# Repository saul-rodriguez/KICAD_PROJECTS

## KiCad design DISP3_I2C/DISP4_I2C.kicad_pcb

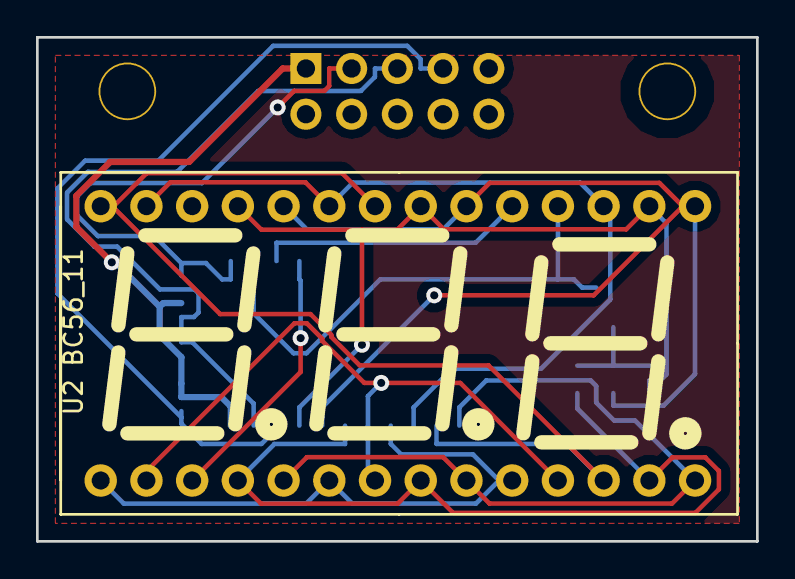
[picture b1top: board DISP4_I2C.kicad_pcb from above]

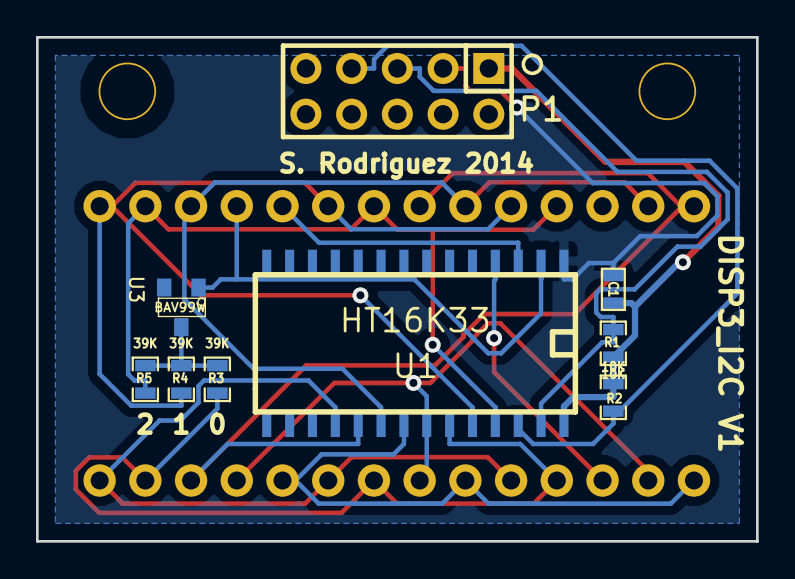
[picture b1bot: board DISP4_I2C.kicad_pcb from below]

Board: 2 copper layers, 40.0 x 28.0 mm, 12 parts (9 on the bottom side), 16 nets.

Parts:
C1: 0.1u; SM0603
P1: CONN_5X2; Pin_Header_Straight_2x05
P2, P3: CONN_1; Mhole
R1, R2: 10K; SM0603_Resistor
R3, R4, R5: 39K; SM0603_Resistor
U1: HT16K33; SO28
U2: BC56_11
U3: BAV99W; SOT23-SPECIAL

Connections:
+5V: C1.1, P1.1, R1.1, R2.1, U1.28
/A: R5.1, U1.25, U2.16, U2.21, U2.25
/B: R4.1, U1.24, U2.15, U2.20, U2.24
/C: R3.1, U1.23, U2.4, U2.8, U2.13
/COM0: U1.2, U2.18, U3.1
/COM1: U1.3, U2.19
/COM2: U1.4, U2.3
/D: U1.22, U2.2, U2.7, U2.11
/DP: U1.18, U2.5, U2.9, U2.14
/E: U1.21, U2.1, U2.6, U2.10
/F: U1.20, U2.17, U2.23, U2.27
/G: U1.19, U2.12, U2.22, U2.28
/SCL: P1.7, R2.2, U1.26
/SDA: P1.5, R1.2, U1.27
GND: C1.2, P1.3, U1.1
unnamed: R3.2, R4.2, R5.2, U3.2

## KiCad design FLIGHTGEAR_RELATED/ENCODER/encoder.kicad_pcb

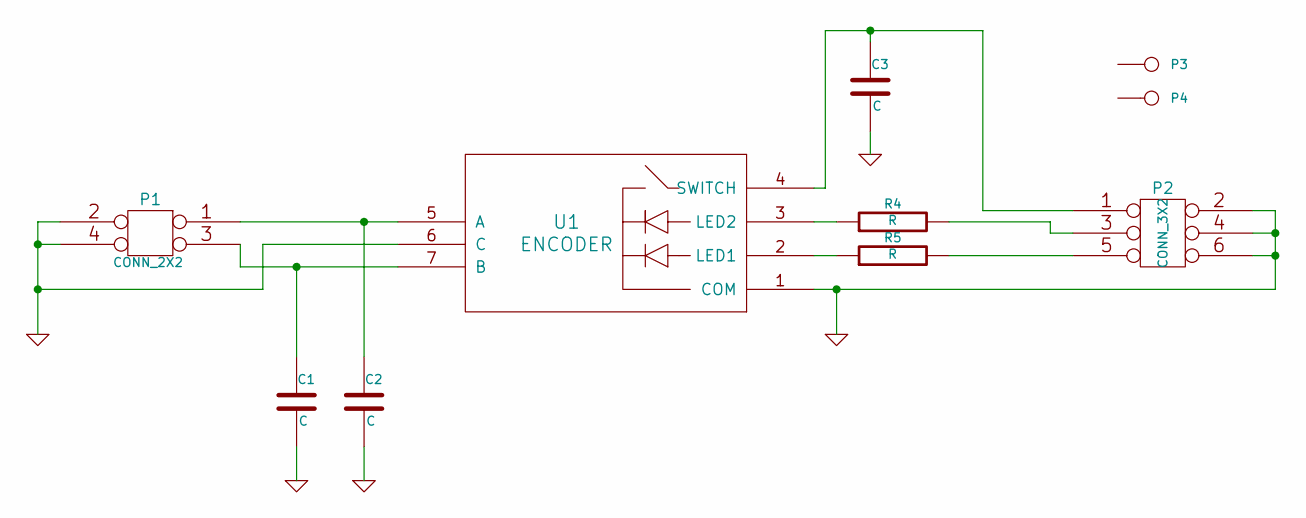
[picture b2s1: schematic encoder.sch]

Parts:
C1, C2, C3: C
P1: CONN_2X2
P2: CONN_3X2
P3, P4: CONN_1
R4, R5: R
U1: ENCODER

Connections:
GND: C1.2, C2.2, C3.2, P1.2, P1.4, P2.2, P2.4, P2.6, U1.1 (COM), U1.6 (C)
unnamed: C1.1, P1.3, U1.7 (B)
unnamed: C2.1, P1.1, U1.5 (A)
unnamed: C3.1, P2.1, U1.4 (SWITCH)
unnamed: P2.3, R4.2
unnamed: P2.5, R5.2
unnamed: R4.1, U1.3 (LED2)
unnamed: R5.1, U1.2 (LED1)

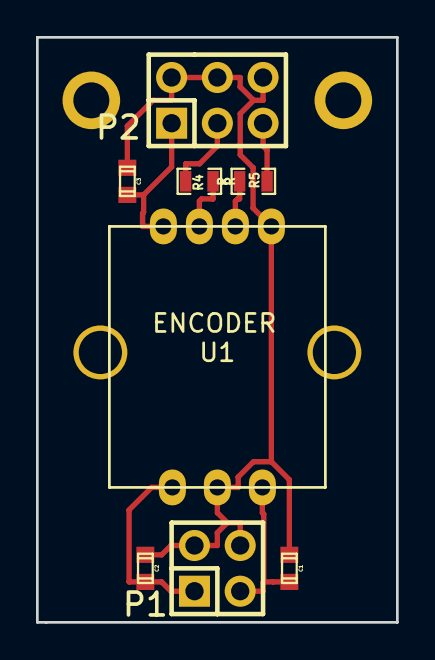
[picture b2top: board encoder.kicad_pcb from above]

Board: 2 copper layers, 20.0 x 32.5 mm, 10 parts (0 on the bottom side), 8 nets.

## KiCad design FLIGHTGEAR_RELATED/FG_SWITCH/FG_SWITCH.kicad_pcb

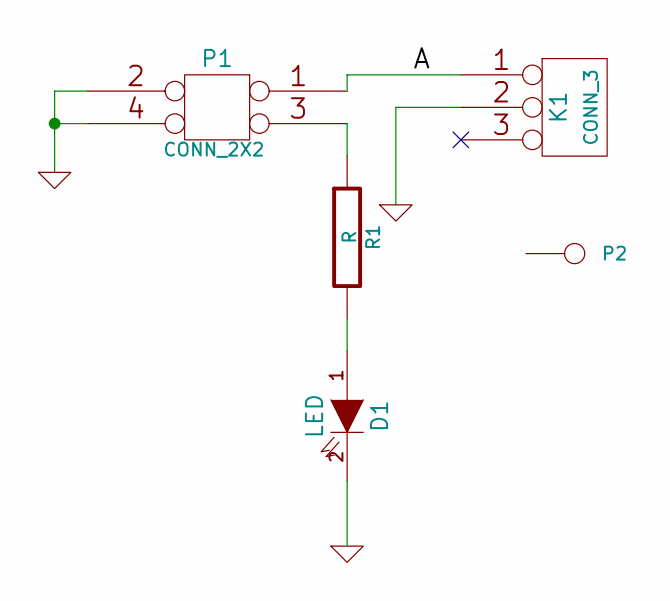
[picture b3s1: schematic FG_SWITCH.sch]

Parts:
D1: LED
K1: CONN_3
P1: CONN_2X2
P2: CONN_1
R1: R

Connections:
/A: K1.1, P1.1
GND: D1.2 (K), K1.2 (PM), P1.2, P1.4
unnamed: D1.1 (A), R1.2
unnamed: P1.3, R1.1

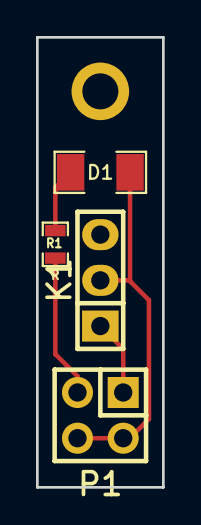
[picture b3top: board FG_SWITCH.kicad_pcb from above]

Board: 2 copper layers, 7.0 x 25.0 mm, 5 parts (0 on the bottom side), 4 nets.

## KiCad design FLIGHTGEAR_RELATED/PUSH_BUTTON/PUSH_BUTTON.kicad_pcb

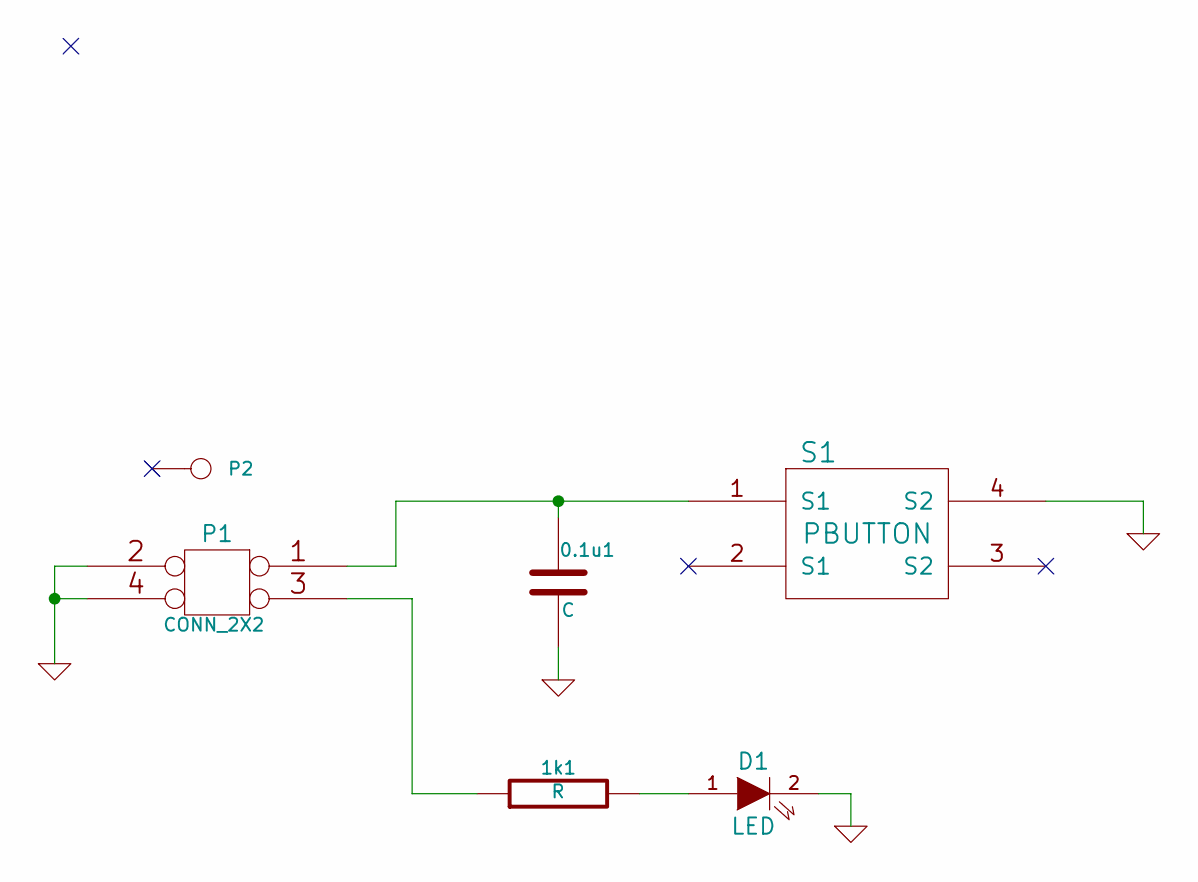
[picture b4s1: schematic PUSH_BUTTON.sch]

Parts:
0.1u1: C
1k1: R
D1: LED
P1: CONN_2X2
P2: CONN_1
S1: PBUTTON

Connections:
GND: 0.1u1.2, D1.2 (K), P1.2, P1.4, S1.4 (S2)
unnamed: 0.1u1.1, P1.1, S1.1 (S1)
unnamed: 1k1.1, P1.3
unnamed: 1k1.2, D1.1 (A)

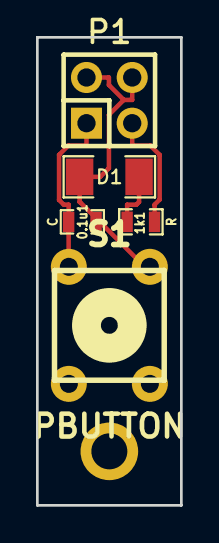
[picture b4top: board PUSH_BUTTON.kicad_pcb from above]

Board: 2 copper layers, 8.0 x 26.0 mm, 6 parts (0 on the bottom side), 4 nets.

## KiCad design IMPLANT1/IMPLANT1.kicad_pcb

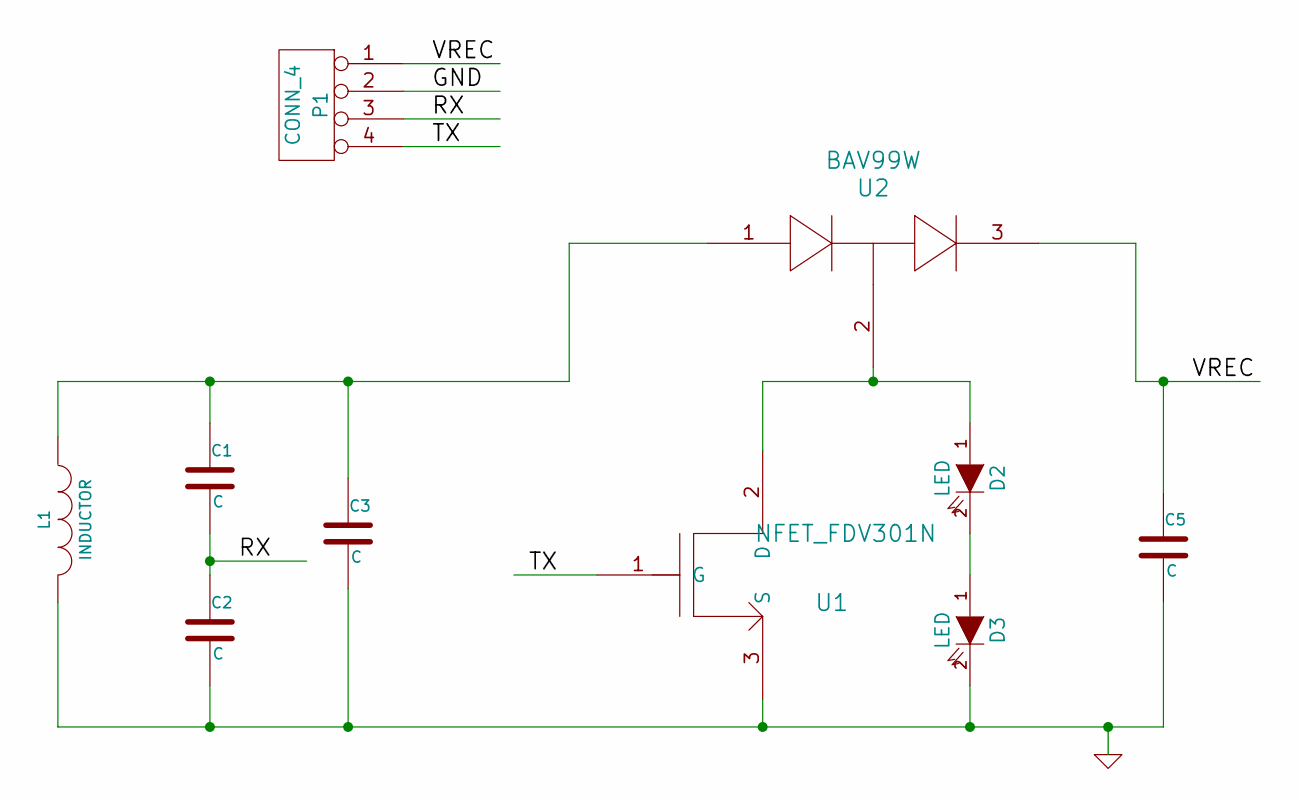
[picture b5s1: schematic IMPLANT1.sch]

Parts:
C1, C2, C3, C5: C
D2, D3: LED
L1: INDUCTOR
P1: CONN_4
U1: NFET_FDV301N
U2: BAV99W

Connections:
/RX: C1.2, C2.1, P1.3
/TX: P1.4, U1.1 (G)
/VREC: C5.1, P1.1, U2.3
GND: C2.2, C3.2, C5.2, D3.2 (K), L1.2, P1.2, U1.3 (S)
unnamed: D2.2 (K), D3.1 (A)
unnamed: D2.1 (A), U1.2 (D), U2.2
unnamed: C1.1, C3.1, L1.1, U2.1

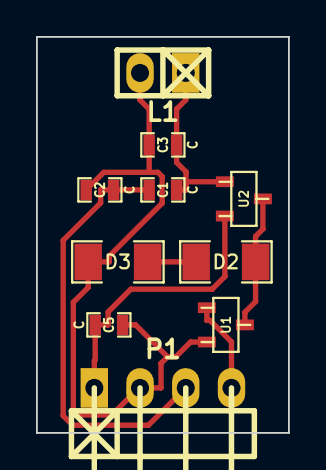
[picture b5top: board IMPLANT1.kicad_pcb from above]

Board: 2 copper layers, 14.0 x 22.0 mm, 10 parts (0 on the bottom side), 7 nets.

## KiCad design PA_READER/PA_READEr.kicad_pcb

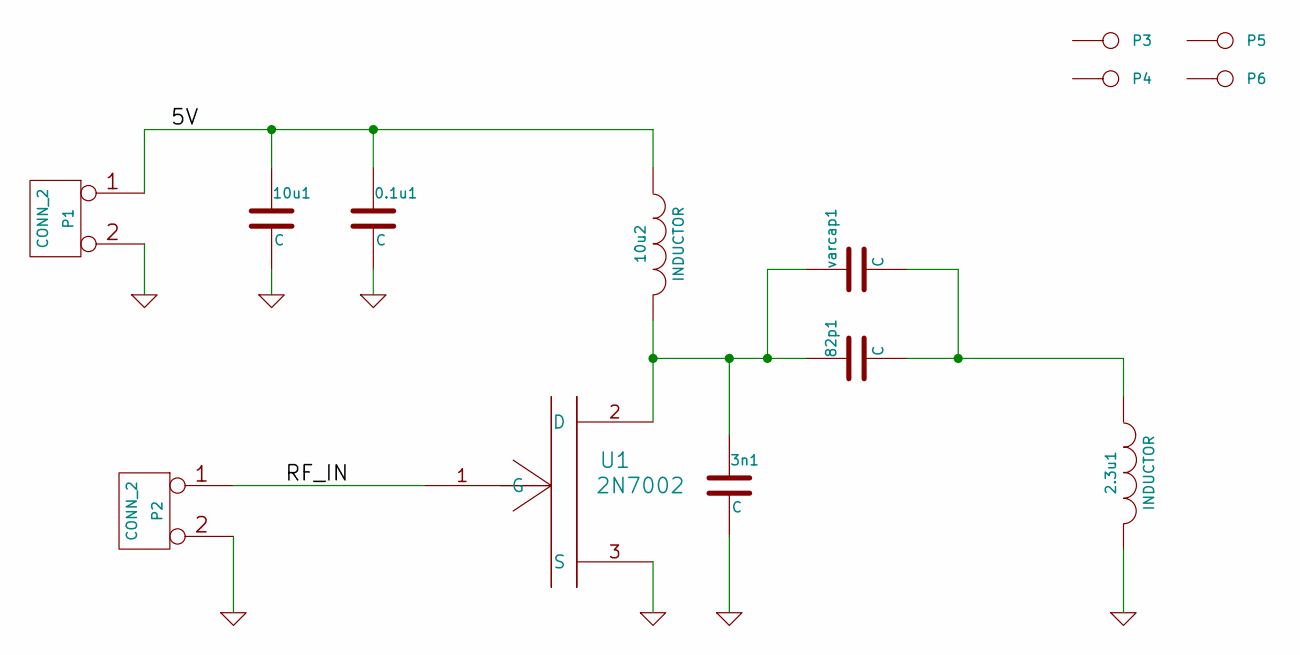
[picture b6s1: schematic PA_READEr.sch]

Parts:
0.1u1, 3n1, 10u1, 82p1: C
2.3u1, 10u2: INDUCTOR
P1, P2: CONN_2
P3, P4, P5, P6: CONN_1
U1: 2N7002
varcap1: C

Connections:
/5V: 0.1u1.1, 10u1.1, 10u2.1, P1.1
/RF_IN: P2.1, U1.1 (G)
GND: 0.1u1.2, 2.3u1.2, 3n1.2, 10u1.2, P1.2 (PM), P2.2 (PM), U1.3 (S)
unnamed: 2.3u1.1, 82p1.2, varcap1.2
unnamed: 3n1.1, 10u2.2, 82p1.1, U1.2 (D), varcap1.1

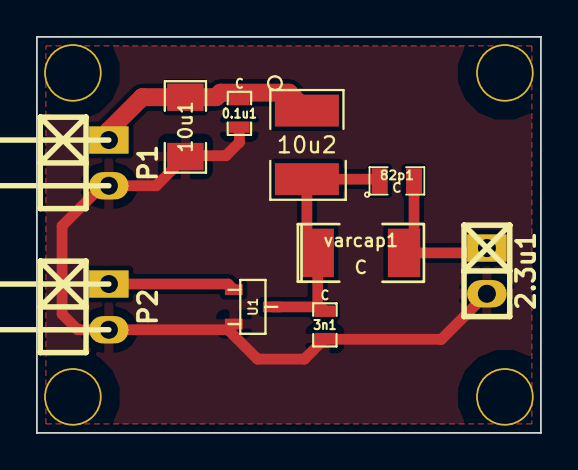
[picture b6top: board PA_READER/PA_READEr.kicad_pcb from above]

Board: 2 copper layers, 28.0 x 22.0 mm, 14 parts (0 on the bottom side), 5 nets.

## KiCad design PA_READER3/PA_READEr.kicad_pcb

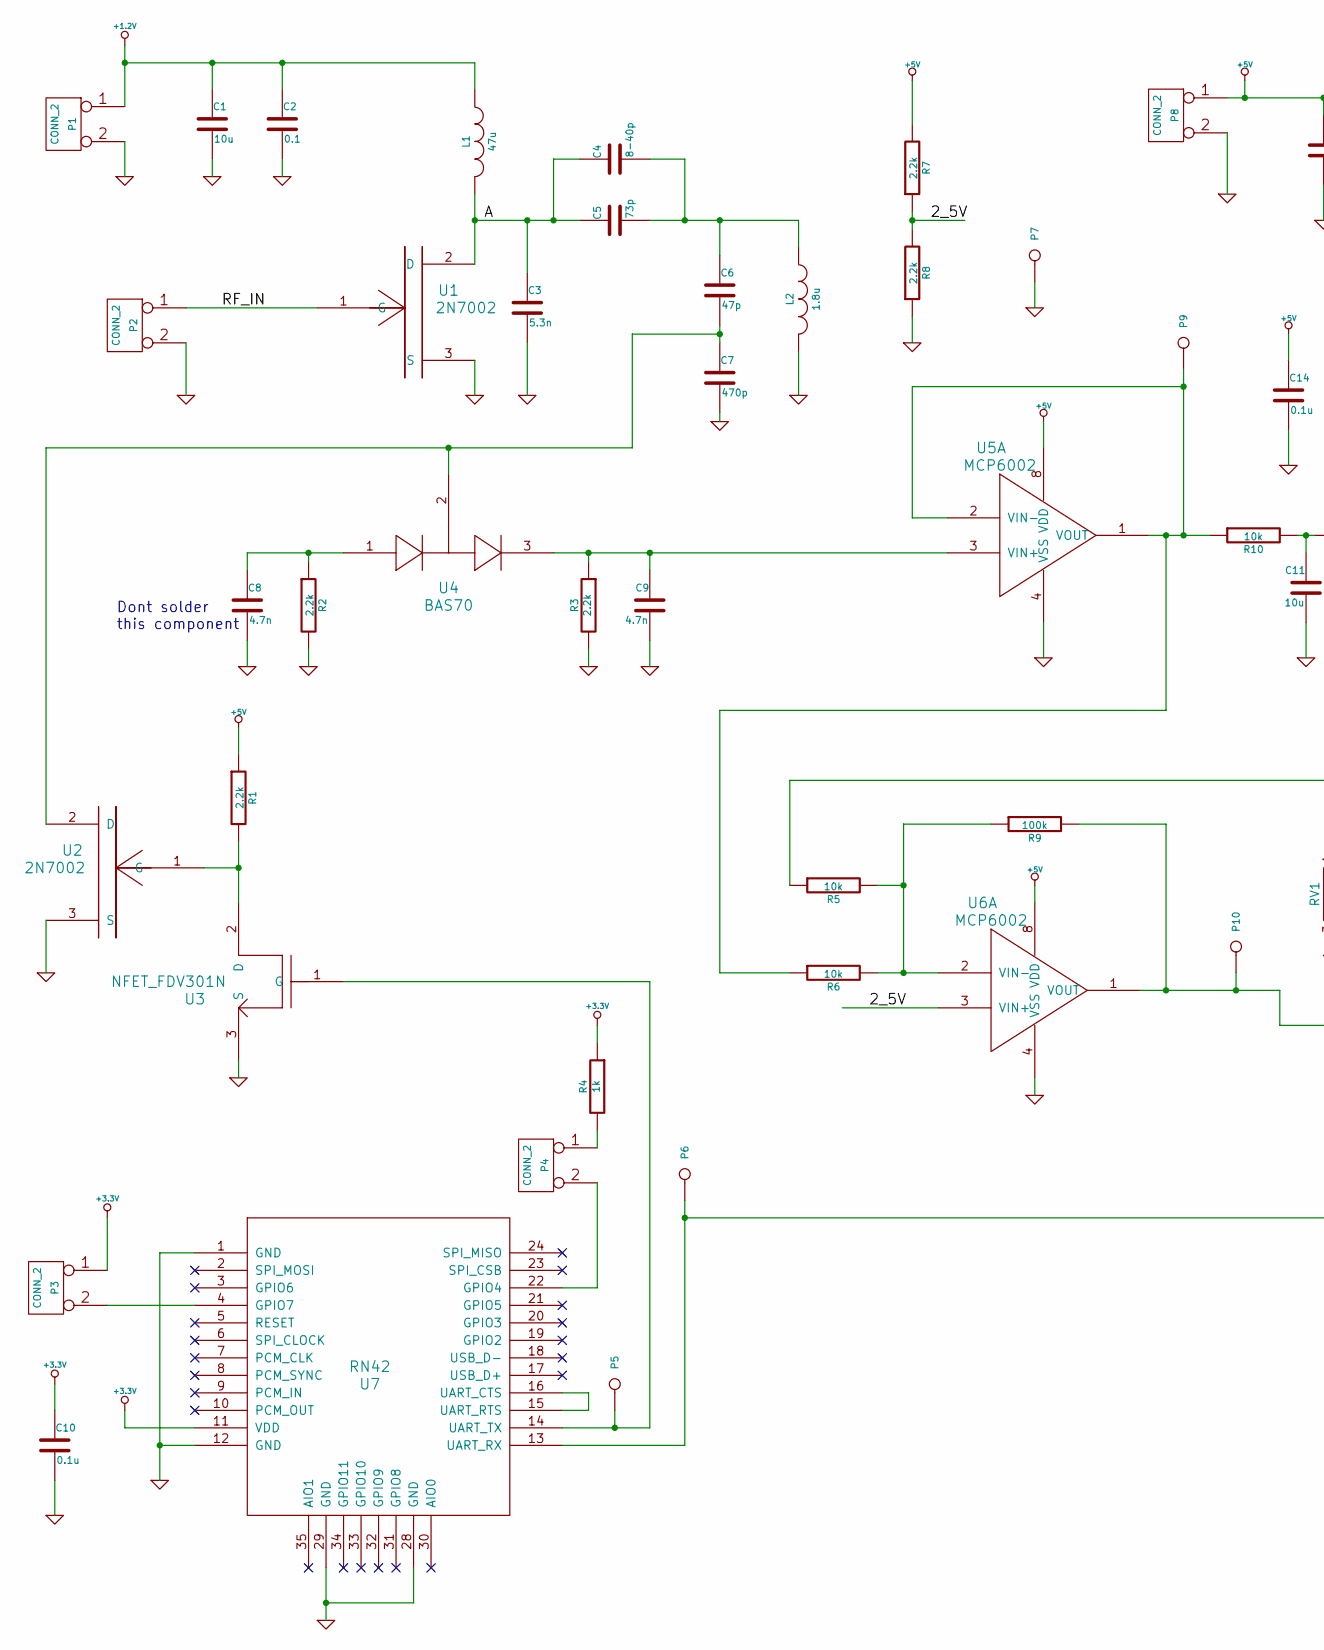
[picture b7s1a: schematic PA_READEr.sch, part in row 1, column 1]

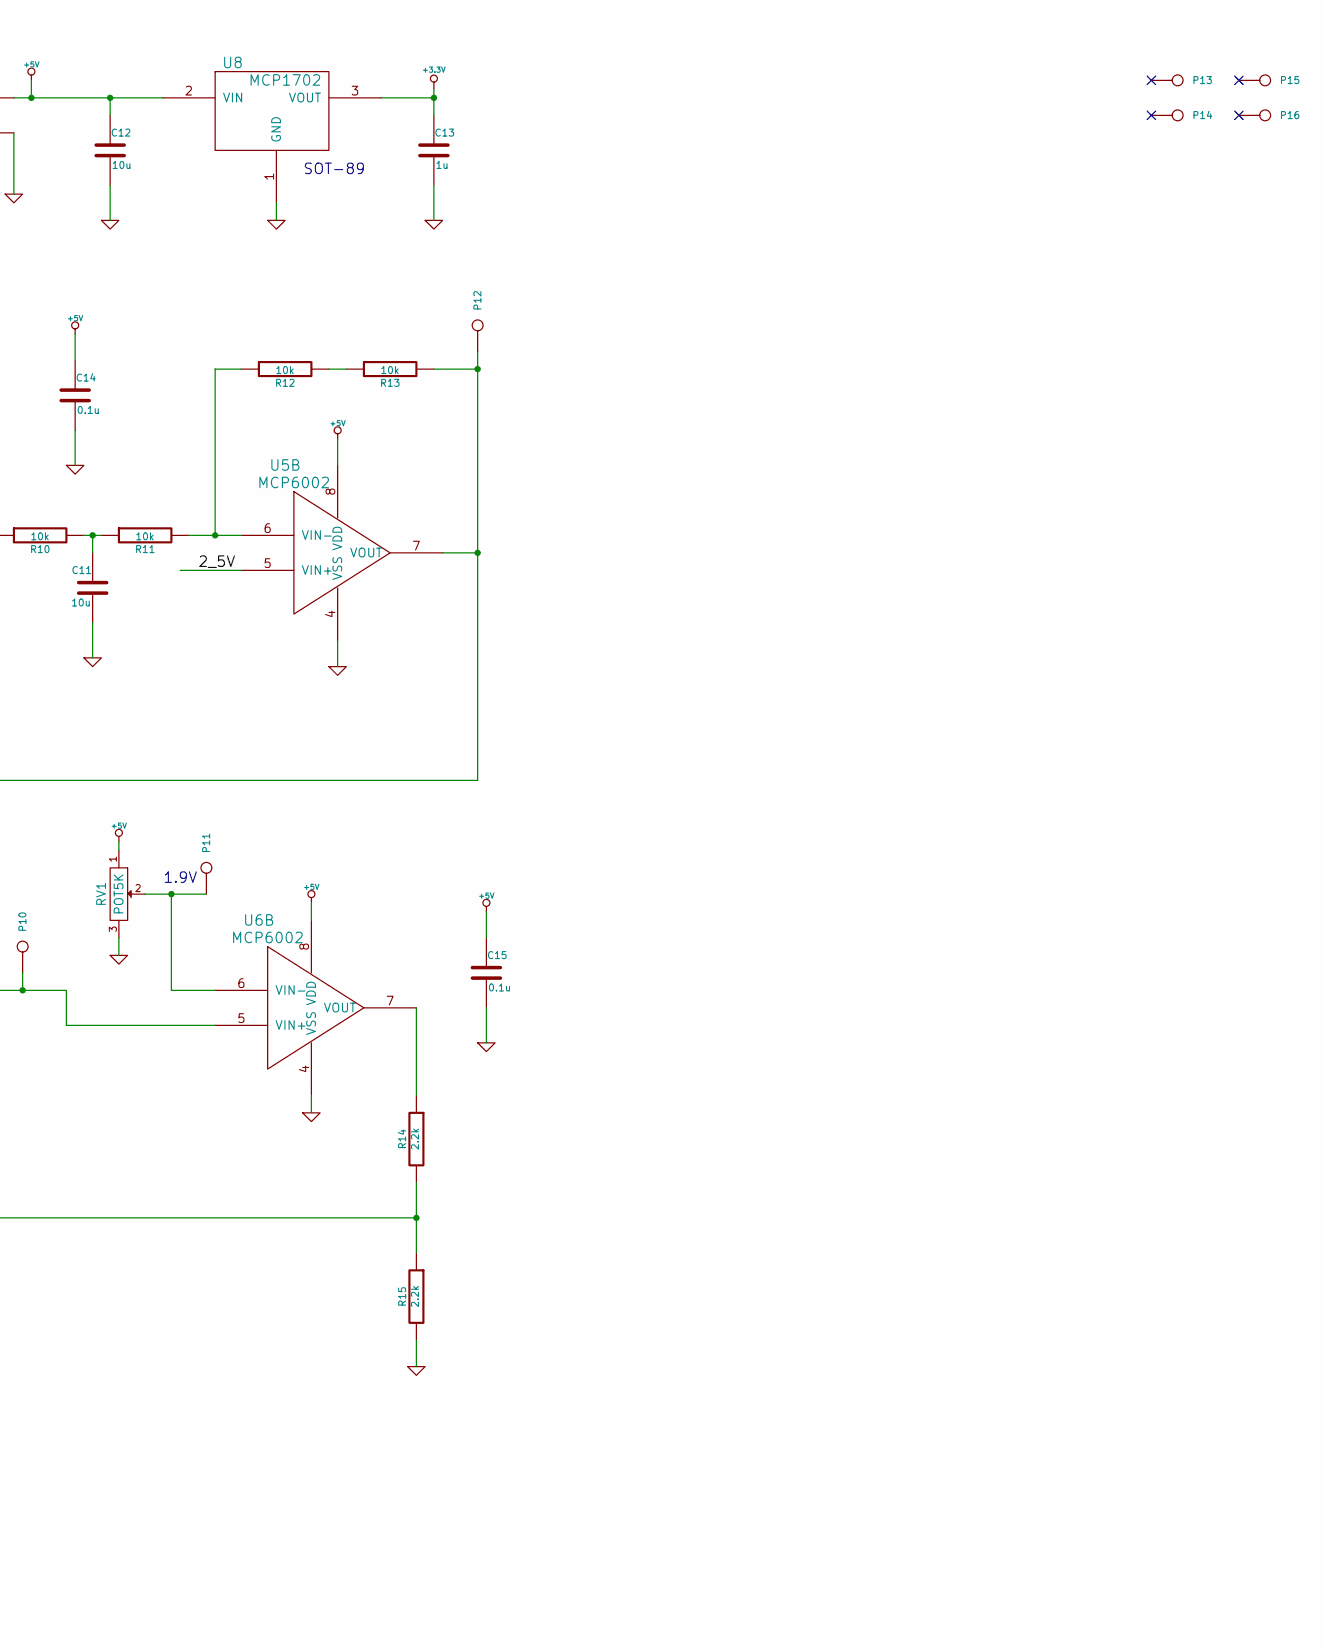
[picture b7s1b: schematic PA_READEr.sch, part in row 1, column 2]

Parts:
C1, C11, C12: 10u
C2: 0.1
C3: 5.3n
C4: 8-40p
C5: 73p
C6: 47p
C7: 470p
C8, C9: 4.7n
C10, C14, C15: 0.1u
C13: 1u
L1: 47u
L2: 1.8u
P1, P2, P3, P4, P8: CONN_2
P5, P6, P7, P9, P10, P11, P12, P13, P14, P15, P16: CONN_1
R1, R2, R3, R7, R8, R14, R15: 2.2k
R4: 1k
R5, R6, R10, R11, R12, R13: 10k
R9: 100k
RV1: POT5K
U1, U2: 2N7002
U3: NFET_FDV301N
U4: BAS70
U5, U6: MCP6002
U7: RN42
U8: MCP1702

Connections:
+1.2V: C1.1, C2.1, L1.1, P1.1
+3.3V: C10.1, C13.1, P3.1, R4.1, U7.11 (VDD), U8.3 (VOUT)
+5V: C12.1, C14.1, C15.1, P8.1, R1.1, R7.2, RV1.1, U5.8 (VDD), U6.8 (VDD), U8.2 (VIN)
/2_5V: R7.1, R8.2, U5.5 (VIN+), U6.3 (VIN+)
/A: C3.1, C4.1, C5.1, L1.2, U1.2 (D)
/RF_IN: P2.1, U1.1 (G)
GND: C1.2, C2.2, C3.2, C7.2, C8.2, C9.2, C10.2, C11.2, C12.2, C13.2, C14.2, C15.2, L2.2, P1.2 (PM), P2.2 (PM), P7.1, P8.2 (PM), R2.2, R3.2, R8.1, R15.2, RV1.3, U1.3 (S), U2.3 (S), U3.3 (S), U5.4 (VSS), U6.4 (VSS), U7.1 (GND), U7.12 (GND), U7.28 (GND), U7.29 (GND), U8.1 (GND)
unnamed: C4.2, C5.2, C6.1, L2.1
unnamed: C6.2, C7.1, U2.2 (D), U4.2
unnamed: C8.1, R2.1, U4.1
unnamed: C9.1, R3.1, U4.3, U5.3 (VIN+)
unnamed: C11.1, R10.2, R11.1
unnamed: P3.2 (PM), U7.4 (GPIO7)
unnamed: P4.1, R4.2
unnamed: P4.2 (PM), U7.22 (GPIO4)
unnamed: P5.1, U3.1 (G), U7.14 (UART_TX)
unnamed: P6.1, R14.2, R15.1, U7.13 (UART_RX)
unnamed: P9.1, R6.1, R10.1, U5.1 (VOUT), U5.2 (VIN-)
unnamed: P10.1, R9.2, U6.1 (VOUT), U6.5 (VIN+)
unnamed: P11.1, RV1.2, U6.6 (VIN-)
unnamed: P12.1, R5.1, R13.2, U5.7 (VOUT)
unnamed: R1.2, U2.1 (G), U3.2 (D)
unnamed: R5.2, R6.2, R9.1, U6.2 (VIN-)
unnamed: R11.2, R12.1, U5.6 (VIN-)
unnamed: R12.2, R13.1
unnamed: R14.1, U6.7 (VOUT)
unnamed: U7.15 (UART_RTS), U7.16 (UART_CTS)

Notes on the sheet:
1.9V
SOT-89
Dont solder this component

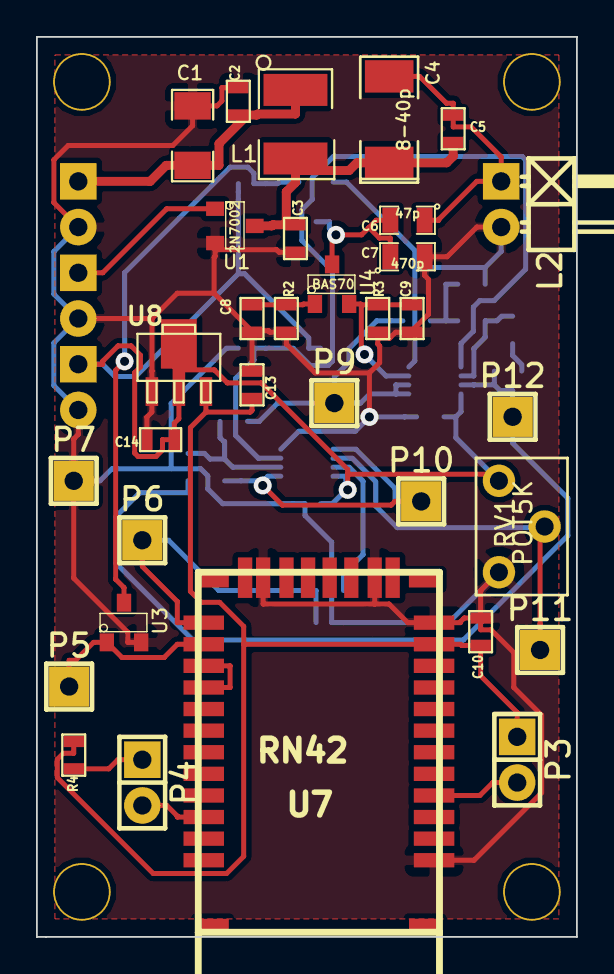
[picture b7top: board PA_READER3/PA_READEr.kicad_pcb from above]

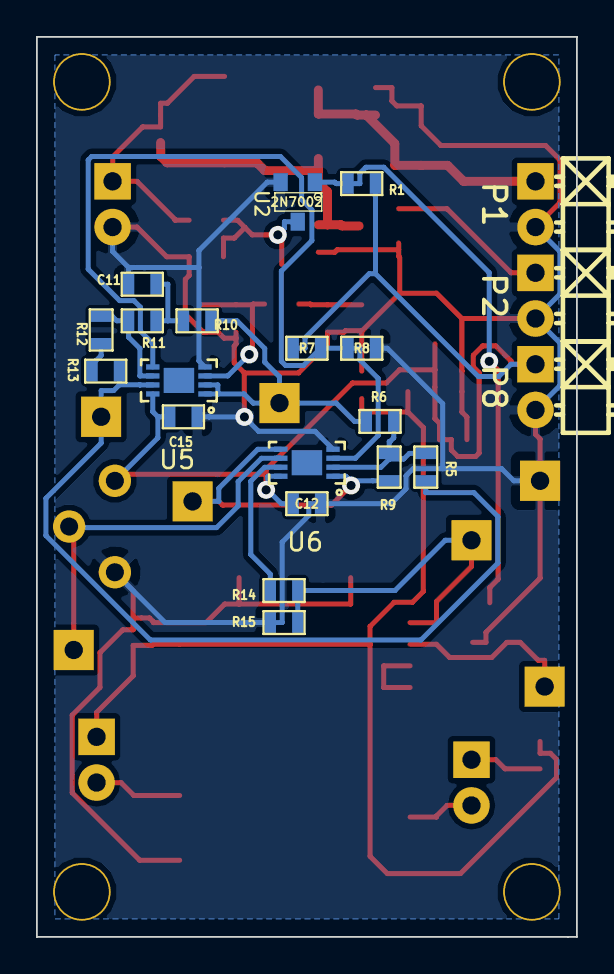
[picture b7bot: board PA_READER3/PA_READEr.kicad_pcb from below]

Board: 2 copper layers, 30.0 x 50.0 mm, 57 parts (21 on the bottom side), 27 nets.
